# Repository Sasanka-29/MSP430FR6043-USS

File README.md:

# 🫁 Spirometer — MSP430FR6043 USS

> An ultrasonic sensing (USS) based incentive spirometer built on the **TI MSP430FR6043** microcontroller, designed for post-surgical lung rehabilitation and respiratory health monitoring.

---

## 📋 Table of Contents

- [About the Project](#about-the-project)
- [What is an Incentive Spirometer?](#what-is-an-incentive-spirometer)
- [System Architecture](#system-architecture)
- [Hardware](#hardware)
- [Technologies Used](#technologies-used)
- [Data Output Methods](#data-output-methods)
- [Repository Structure](#repository-structure)
- [Getting Started](#getting-started)
- [Roadmap](#roadmap)
- [Contributing](#contributing)
- [License](#license)

---

## 📖 About the Project

This project implements a **digital incentive spirometer** using the **MSP430FR6043** microcontroller's built-in **Ultrasonic Sensing Solution (USS)** module. The USS module measures airflow through an ultrasonic transducer pair, enabling accurate, non-mechanical spirometry readings.

**Key Highlights:**

- 🔊 Ultrasonic time-of-flight (ToF) based flow measurement — no moving parts
- 🎯 Calibrated using the **TI USS Design Center GUI**
- 💻 Firmware developed in **Code Composer Studio (CCS)**
- 📡 Dual data output: **USS GUI** or **UART serial communication**
- 🖥️ Custom **Python GUI** for real-time 4-channel data visualization
- 🔧 Planned migration from the **EVM430-FR6043** evaluation module to a **custom PCB** with hardware optimizations

---

## 💡 What is an Incentive Spirometer?

An **incentive spirometer** is a handheld medical device used to exercise and expand the lungs. It is commonly prescribed:

- **After surgery** — to prevent pulmonary complications during recovery
- **After chest/lung injury** — to restore lung capacity
- **During illness** — to reduce the risk of pneumonia and atelectasis (lung collapse)

The device encourages patients to take slow, deep breaths, helping keep the alveoli (air sacs) open and improving oxygen exchange.

### Why Digitize It?

Traditional incentive spirometers are purely mechanical — a ball or piston rises in a chamber as the patient inhales. This project aims to **digitize** the incentive spirometer using ultrasonic flow sensing, enabling:

| Feature           | Traditional          | This Project                     |
| ----------------- | -------------------- | -------------------------------- |
| Measurement       | Visual (ball height) | Precise digital values           |
| Data Logging      | ❌ None              | ✅ CSV export & real-time graphs |
| Remote Monitoring | ❌ Not possible      | ✅ UART / future wireless        |
| Accuracy          | Approximate          | IEEE 754 float precision         |
| Moving Parts      | Yes (ball/piston)    | None (ultrasonic)                |

---

## 🏗️ System Architecture

```mermaid
flowchart TD
    Transducers["Ultrasonic Transducers<br/>(Upstream & Downstream)"]

    MSP["MSP430FR6043<br/>USS Module (ToF Measurement)<br/>Signal Processing & Firmware"]

    GUI["USS GUI<br/>(TI Design Center)<br/><br/>• Calibration<br/>• Visualization<br/>• Debugging"]

    subgraph UART ["UART Output (Serial → PC)"]
        direction TB
        Script1["uart_parse.py<br/>(CLI batch)"]
        Script2["uart_gui.py<br/>(Live GUI)"]
    end

    Transducers --> MSP
    MSP --> GUI
    MSP --> UART
```

---

## 🔧 Hardware

### Current Development Platform

| Component       | Details                                                                  |
| --------------- | ------------------------------------------------------------------------ |
| **MCU**         | [TI MSP430FR6043](https://www.ti.com/product/MSP430FR6043)               |
| **Dev Board**   | [EVM430-FR6043](https://www.ti.com/tool/EVM430-FR6043) Evaluation Module |
| **Sensing**     | Ultrasonic Sensing Solution (USS) — Time-of-Flight                       |
| **Transducers** | Upstream & downstream ultrasonic transducer pair                         |
| **IDE**         | [Code Composer Studio (CCS)](https://www.ti.com/tool/CCSTUDIO)           |
| **Calibration** | [TI USS Design Center GUI](https://www.ti.com/tool/USS-DESIGN-CENTER)    |

### Planned Custom PCB

The next phase of this project involves designing a **custom PCB** to replace the EVM430-FR6043, with the following goals:

- 🔩 **Hardware optimization** — reduced board size, optimized power routing
- ⚡ **Low power design** — leveraging MSP430FR6043 ultra-low-power modes (LPM3/LPM4)
- 🧩 **Application-specific layout** — tailored for spirometer enclosure integration
- 📡 **Communication interfaces** — UART, potential wireless (BLE/Wi-Fi) add-on
- 🔋 **Battery operation** — portable, handheld device form factor

---

## 🛠️ Technologies Used

### Firmware / Embedded

| Technology           | Purpose                                   |
| -------------------- | ----------------------------------------- |
| MSP430FR6043         | Ultra-low-power MCU with USS module       |
| USS Library          | TI's ultrasonic sensing signal processing |
| Code Composer Studio | IDE for firmware development              |
| USS Design Center    | Transducer calibration & flow config      |

### Software / Host PC

| Technology  | Purpose                            |
| ----------- | ---------------------------------- |
| Python 3.7+ | Host-side data acquisition scripts |
| pyserial    | Serial UART communication          |
| matplotlib  | Real-time 4-channel graph plotting |
| Tkinter     | GUI framework for serial monitor   |

---

## 📤 Data Output Methods

There are **two methods** to obtain spirometry readings from the MSP430FR6043:

### Method 1: USS Design Center GUI

| Aspect          | Details                             |
| --------------- | ----------------------------------- |
| **Connection**  | USB to EVM430-FR6043                |
| **Software**    | TI USS Design Center GUI            |
| **Best For**    | Development, calibration, debugging |
| **Data Format** | Visual plots + internal data export |

### Method 2: UART Communication ⭐

| Aspect          | Details                                                   |
| --------------- | --------------------------------------------------------- |
| **Connection**  | USB/Serial to MSP430FR6043                                |
| **Software**    | `uart_gui.py` (live) or `uart_parse.py` (batch)           |
| **Best For**    | Standalone operation, data logging, integration           |
| **Data Format** | `<delimiter>,<hex IEEE754>` → decoded float               |
| **Channels**    | AbsTof-UPS (`$`), AbsTof-DNS (`#`), DToF (`%`), VFR (`!`) |

> 📖 **See the full UART documentation:** [`Spirometer/UART/README.md`](Spirometer/UART/README.md)

---

## 📁 Repository Structure

```
MSP430FR6043-USS/
│
├── 📄 README.md                            ← You are here
│
└── 📂 Spirometer/
    │
    ├── 📂 GUI/                             ← USS Design Center GUI files
    │   └── README.md                       ← GUI module documentation
    │
    └── 📂 UART/                            ← UART communication module
        ├── 📄 README.md                    ← Detailed UART documentation
        ├── 🐍 uart_parse.py                ← CLI batch hex → float parser
        ├── 🐍 uart_gui.py                  ← Real-time serial monitor GUI
        ├── 📊 hex_in.csv                   ← Sample raw UART data (hex)
        ├── 📊 hex_out.csv                  ← Sample decoded output (float)
        └── 📄 tempCodeRunnerFile.python    ← Dev temp file (VS Code)
```

---

## 🚀 Getting Started

### Prerequisites

| Requirement                  | Link                                                  |
| ---------------------------- | ----------------------------------------------------- |
| Code Composer Studio (CCS)   | [Download](https://www.ti.com/tool/CCSTUDIO)          |
| TI USS Design Center GUI     | [Download](https://www.ti.com/tool/USS-DESIGN-CENTER) |
| EVM430-FR6043 (or custom HW) | [Product Page](https://www.ti.com/tool/EVM430-FR6043) |
| Python 3.7+                  | [Download](https://www.python.org/downloads/)         |
| USB Cable                    | For programming & UART                                |

### Quick Start

1. **Clone the repository**

   ```bash
   git clone https://github.com/Sasanka-29/MSP430FR6043-USS.git
   cd MSP430FR6043-USS
   ```

2. **Install Python dependencies** (for UART tools)

   ```bash
   pip install pyserial matplotlib
   ```

3. **Firmware Setup**
   - Open Code Composer Studio
   - Import the project from the `Spirometer/` directory
   - Connect the EVM430-FR6043 via USB

4. **Calibrate using USS Design Center**
   - Open the USS Design Center GUI
   - Follow the calibration workflow for your transducer configuration

5. **Flash and Run**
   - Build and flash the firmware to the MSP430FR6043

6. **View Output**

   **Option A — USS GUI:**
   Use the TI Design Center for visualization

   **Option B — UART (Recommended for data logging):**

   ```bash
   # Real-time GUI monitor
   cd Spirometer/UART
   python uart_gui.py

   # Or batch parse captured data
   python uart_parse.py hex_in.csv hex_out.csv
   ```

---

## 🗺️ Roadmap

- [x] Initial firmware development on EVM430-FR6043
- [x] USS Design Center GUI calibration
- [x] UART data output implementation
- [x] Python CLI parser (`uart_parse.py`)
- [x] Real-time serial monitor GUI (`uart_gui.py`)
- [x] Custom PCB schematic design
- [x] Custom PCB layout and fabrication
- [x] Hardware optimization and power profiling
- [ ] Enclosure design for handheld spirometer
- [ ] Patient-facing display/indicator integration
- [ ] Wireless data transmission (BLE/Wi-Fi)
- [ ] Mobile app integration

---

## 🤝 Contributing

Contributions are welcome! If you'd like to improve this project:

1. **Fork** the repository
2. **Create** a feature branch (`git checkout -b feature/your-feature`)
3. **Commit** your changes (`git commit -m 'Add your feature'`)
4. **Push** to the branch (`git push origin feature/your-feature`)
5. **Open** a Pull Request

### Ideas for Contribution

- 📐 Custom PCB design files (KiCad/Altium)
- 📱 Mobile app for Bluetooth data reception
- 📊 Advanced spirometry analytics (FEV1, FVC calculation)
- 🧪 Unit tests for the Python parsing scripts
- 📝 Additional documentation or translations

---

## 📄 License

Distributed under the MIT License. See [`LICENSE`](LICENSE) for more information.

---

## 📚 References

- [MSP430FR6043 Product Page](https://www.ti.com/product/MSP430FR6043) — TI microcontroller datasheet & resources
- [USS Design Center User Guide](https://www.ti.com/tool/USS-DESIGN-CENTER) — Calibration and configuration tool
- [EVM430-FR6043 User Guide](https://www.ti.com/tool/EVM430-FR6043) — Evaluation module documentation
- [MSP430 USS Application Report (SLAA720)](https://www.ti.com/lit/an/slaa720c/slaa720c.pdf) — Ultrasonic sensing implementation guide

---

<p align="center">
  <b>Designed & Developed by <a href="https://github.com/Sasanka-29">Sasanka-29</a></b><br>
  <i>MSP430FR6043 Ultrasonic Sensing Solution — Incentive Spirometer</i><br><br>
  ⭐ Star this repo if you find it useful!
</p>

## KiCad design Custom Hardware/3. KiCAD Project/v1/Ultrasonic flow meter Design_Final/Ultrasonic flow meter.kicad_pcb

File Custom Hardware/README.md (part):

# MSP430FR6043 USS - Custom Hardware Documentation

## Overview

This directory contains the **complete custom hardware design assets, documentation, and validation records** for the `MSP430FR6043_USS` project. It supports development, validation, and long-term maintenance of hardware built around the **Texas Instruments MSP430FR6043** microcontroller with **Ultrasonic Sensing Solution (USS)** capabilities.

> **For Firmware/Software:** Refer to the repository root and source directories for application code, bootloader, and USS driver implementations.  
> **This folder focuses on:** Board-level hardware artifacts, schematics, PCB layouts, BOMs, bring-up procedures, and validation evidence.

---

## Table of Contents

1. [Project Objectives](#1-project-objectives)
2. [Hardware Overview](#2-hardware-overview)
3. [Design Principles](#3-design-principles)
4. [Directory Structure](#4-directory-structure)
5. [Hardware Revisions](#5-hardware-revisions)
6. [Pin Assignment & Interfaces](#6-pin-assignment--interfaces)
7. [Power, Ground & Clock Design](#7-power-ground--clock-design)
8. [Programming & Bring-Up Procedure](#8-programming--bring-up-procedure)
9. [Validation & Testing](#9-validation--testing)
10. [Manufacturing Checklist](#10-manufacturing-checklist)
11. [Bill of Materials (BOM)](#11-bill-of-materials-bom)
12. [Firmware Compatibility](#12-firmware-compatibility)
13. [Known Issues & Limitations](#13-known-issues--limitations)
14. [Contributing Guidelines](#14-contributing-guidelines)
15. [To Do & Future Work](#15-to-do--future-work)
16. [References & Resources](#16-references--resources)
17. [Maintenance & Handoff](#17-maintenance--handoff)
18. [License & Compliance](#18-license--compliance)

---

## 1) Project Objectives

The MSP430FR6043 USS custom hardware platform enables:

### Primary Goals
- **Prototype Development:** Rapid hardware iteration for ultrasonic sensing applications
- **Performance Validation:** Characterize power consumption, signal integrity, and real-time behavior
- **Peripheral Integration:** Test and validate all external interfaces (UART, GPIO, analog inputs, programming headers)
- **Hardware-Firmware Co-Development:** Ensure seamless integration between hardware design and firmware implementation
- **Reproducibility:** Create a baseline for manufacturing, field deployment, and long-term support

### Key Principles
- **Traceability:** Every design decision is documented with rationale and evidence
- **Reproducibility:** Future developers can rebuild and validate with confidence
- **Maintainability:** Clear documentation minimizes debug cycles and institutional knowledge loss
- **Scalability:** Support multiple board revisions while maintaining backward compatibility

---

## 2) Hardware Overview

### System Architecture

The MSP430FR6043 platform consists of:

| Subsystem | Components | Purpose |
|-----------|-----------|---------|
| **MCU Core** | MSP430FR6043 + support circuitry | Primary processing and USS interface |
| **Power Distribution** | Voltage regulators, decoupling capacitors, protection circuits | Stable supply for analog and digital domains |
| **Clock Network** | Crystal oscillator, load capacitors | Precise timing for USS and real-time operations |
| **Debug Interface** | JTAG/SBW header, test points | Programming and in-circuit debugging |
| **Ultrasonic Front-End** | Transducer interface, signal conditioning | USS signal acquisition and processing |
| **I/O & Test Points** | Headers, connectors, measurement hooks | System bring-up and signal observation |

### Design Constraints
- Low-noise analog performance (USS operates in 40-100 kHz range)
- Low-power operation (MSP430FR6043 FRAM architecture)
- Reliable programming access (no conflicts with application I/O)
- Practical manufacturability and PCB testability

---

## 3) Design Principles

### Analog Signal Integrity
1. Separate analog and digital ground planes where applicable
2. Keep USS signal paths isolated from high-speed digital switching
3. Place decoupling capacitors within 5mm of supply pins
4. Use star grounding at measurement reference points

### Power Management
1. Clean regulated supplies for both analog and digital domains
2. Adequate bulk and bypass capacitance per datasheet recommendations
3. Transient protection for external inputs (ESD, overcurrent)
4. Isolation strategy for programming pins from application circuitry

### Clock Design
1. Crystal oscillator with proper load matching
2. Minimal EMI radiation from clock traces
3. Startup verification at multiple supply voltages
4. Characterization data recorded for production batches

---

## 4) Directory Structure

Current folder organization:

```
Custom Hardware/
├── README.md                              # This file
├── Custom Board Connections/              # Board-level connection documentation and interfaces
├── Issues and Fixes for Custom Boards/    # Known issues, bug reports, and resolution procedures
├── KiCAD Project/                         # KiCAD schematic and PCB design files
├── Spirometer latest 3D Files/            # 3D CAD models and mechanical drawings for enclosure/mounting
├── Spirometer Dimension diagram/          # Dimensional specifications and mechanical diagrams
├── Assembly Guide/                        # Hardware assembly instructions and procedures
├── Zero Flow Calibration Setup/           # Calibration procedures and reference data
└── Results/                               # Test results, validation data, and performance logs
```

### Folder Descriptions

- **Custom Board Connections:** Documentation of all board connectors, headers, and external interfaces
- **Issues and Fixes for Custom Boards:** Hardware issues discovered during development, troubleshooting guides, and workarounds
- **KiCAD Project:** Complete KiCAD project files including schematics, PCB layouts, and design outputs
- **Spirometer latest 3D Files:** 3D CAD models for mechanical components, enclosure designs, and mounting brackets
- **Spirometer Dimension diagram:** Technical drawings with dimensional specifications and mechanical tolerances
- **Assembly Guide:** Step-by-step hardware assembly procedures, BOM details, and bring-up procedures
- **Zero Flow Calibration Setup:** Calibration baseline data and procedures for zero-flow reference conditions
- **Results:** Performance validation results, power measurements, USS characterization logs, and test reports

---

## 5) Hardware Revisions

### Revision Tracking Table

| Revision | Status | Release Date | Summary | Key Changes | Firmware Impact | Validation |
|----------|--------|--------------|---------|------------|-----------------|------------|
| REV_A | Released | TBD | Initial prototype | First production run | Baseline | Complete |
| REV_B | Planning | TBD | Analog improvements | Front-end filtering updates | Recalibration | Pending |

### For Each Revision, Document:
- **Design Changes:** Specific modifications and rationale
- **Affected Signals:** Which nets/interfaces changed
- **Firmware Implications:** Pin mappings, calibration constants, driver updates
- **Validation Evidence:** Test data, measurements, approval sign-offs
- **Known Issues:** Bugs, workarounds, or limitations specific to this revision

---

## 6) Pin Assignment & Interfaces

### MCU Pin Mapping

Maintain a detailed pin-assignment matrix (create `Pin_Assignment_Matrix.xlsx` or similar):

| MCU Pin | Signal Name | Board Function | Peripheral | Firmware Symbol | Schematic Reference | Notes |
|---------|------------|-----------------|------------|-----------------|-------------------|-------|
| P1.0 | GPIO_0 | Example I/O | GPIO | PIN_IO_0 | U1-1 | TBD |
| P2.0 | USS_RX | Ultrasonic RX | USS | PIN_USS_RX | J1-2 | Analog input |

### External Interfaces

Document all connectors and headers:

- **Power Input:** Voltage requirements, polarity, protection
- **Debug/JTAG:** Pin layout, support toolchain
- **UART/Serial:** Baud rates, connector type
- **Analog Inputs/Outputs:** Signal ranges, impedance, termination
- **Test Points:** Measurement access points with expected voltage ranges

---

## 7) Power, Ground & Clock Design

### Power Distribution

**Supply Rails:**
- Input voltage range: [TBD] V
- Regulated output: [TBD] V @ [TBD] mA max
- Quiescent current: [TBD] mA (typical)

**Decoupling Strategy:**
- MCU supply: 100nF + 10µF (close placement)
- Analog supply: 100nF + 10µF (if separate)
- Bulk capacitance: 47µF (for transient loading)

### Ground Design
- Multi-point ground connection at board entry
- Ground plane continuity under critical traces
- Star grounding at measurement reference points

### Clock Network
- **Oscillator Frequency:** [TBD] MHz
- **Load Capacitance:** [TBD] pF
- **Startup Time:** < [TBD] ms
- **Frequency Stability:** ±[TBD] ppm

### Measured Characteristics (per revision)
- Rail ripple and transient response
- Startup behavior and settling time
- Current profiles by operational mode
- Temperature/voltage drift (if applicable)

---

## 8) Programming & Bring-Up Procedure

### Pre-Power Checklist
- [ ] Visual inspection: polarity, solder joints, shorts
- [ ] Continuity check on critical nets
- [ ] No visible damage or bridged pads

### Power-On Validation
- [ ] Apply input voltage slowly (observe current ramp)
- [ ] Measure all regulated rails and confirm nominal values
- [ ] Check quiescent current against expectations
- [ ] Verify no shorts (current should plateau)

### Programming & Debug
- [ ] Connect JTAG/SBW debugger
- [ ] Verify connection in IDE or debugger software
- [ ] Flash known-good test image
- [ ] Verify successful programming (LED blink test, etc.)

### Peripheral Validation
- [ ] UART loopback test (if applicable)
- [ ] GPIO output test (LED flash, test point measurement)
- [ ] Timer/counter verification
- [ ] Analog input verification (known voltage sources)

### USS Functional Test
- [ ] Connect transducer or known signal source
- [ ] Run USS calibration routine
- [ ] Compare output signatures with baseline
- [ ] Document results and save logs

### Post-Validation
- [ ] Document board ID, test date, operator name
- [ ] Archive photos (top, bottom, detail shots)
- [ ] Save measurement data and logs
- [ ] Mark board as "ready for deployment" or "needs rework"

---

## 9) Validation & Testing

### Required Evidence per Revision

Each board revision must include:

- **Bring-Up Logs:** Dated records with board ID, firmware hash, test results
- **Power Measurements:** Active/idle/LPM current, rail ripple, startup transients
- **Oscillator Characterization:** Frequency, stability across voltage/temperature
- **USS Validation:** Functional signatures, calibration data, response plots
- **Peripheral Tests:** UART, GPIO, timer, analog, all working as documented
- **Failure Analysis:** Any issues encountered, root cause, resolution

### Validation Checklist
- [ ] Board photos (top, bottom, detail)
- [ ] Power rails measured and documented
- [ ] Program successful with known-good image
- [ ] All peripherals respond correctly
- [ ] USS functional with baseline transducer
- [ ] No unexpected behavior or regressions
- [ ] Logs and measurement data archived

---

## 10) Manufacturing Checklist

Before release to fabrication or production:

### Design Verification
- [ ] Schematic schematic reviewed and approved
- [ ] ERC (electrical rule check) passed
- [ ] DRC (design rule check) passed on PCB
- [ ] Design review sign-off documented

### Fabrication Package
- [ ] Gerber files generated and verified
- [ ] Drill file included with correct formats
- [ ] Soldermask/silkscreen layers correct
- [ ] PCB stackup and layer order documented
- [ ] File naming consistent (REV tag in filenames)

### Assembly Package
- [ ] BOM exported with MPN, manufacturer, quantity
- [ ] Pick-and-place file generated
- [ ] Assembly drawing with reference designators
- [ ] Component orientation clearly marked
- [ ] All footprints match BOM parts

### Quality & Testing
- [ ] Test-point map generated
- [ ] Bring-up procedure finalized
- [ ] Test image and firmware version noted
- [ ] Acceptance criteria defined
- [ ] Quality checklist ready for manufacturing

---

## 11) Bill of Materials (BOM)

### BOM Format

Maintain BOM as `BOM_REV_X.xlsx` or `.csv` with columns:

| Item | Reference(s) | Description | Manufacturer | MPN | Alt. MPN | Package | Qty | Unit Cost | Lead Time | Lifecycle | Risk Notes |
|------|---------|-------------|----------|-----|----------|---------|-----|-----------|-----------|-----------|-----------|
| 1 | U1 | MCU | Texas Instruments | MSP430FR6043IRHAT | - | LQFP-64 | 1 | $[TBD] | [TBD] weeks | Active | Low |

### Critical BOM Notes
- **Lifecycle Status:** Active / NRND / Obsolete
- **Approved Alternates:** Part numbers with compatible footprints/function
- **Supply Constraints:** Single-source risks, long lead items
- **Environmental:** Temperature ratings, RoHS compliance, moisture sensitivity

---

## 12) Firmware Compatibility

### Compatibility Matrix

| Hardware Revision | Firmware Version/Tag | Tested By | Date | Notes | Calibration Required |
|------------------|------------------|-----------|------|-------|----------------------|
| REV_A | v1.0.0 | [Name] | [Date] | Initial release | Yes |
| REV_B | v1.1.0+ | [Name] | [Date] | Updated front-end filtering | Yes |

### Version Management
- Tag firmware releases that are validated for each hardware revision
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
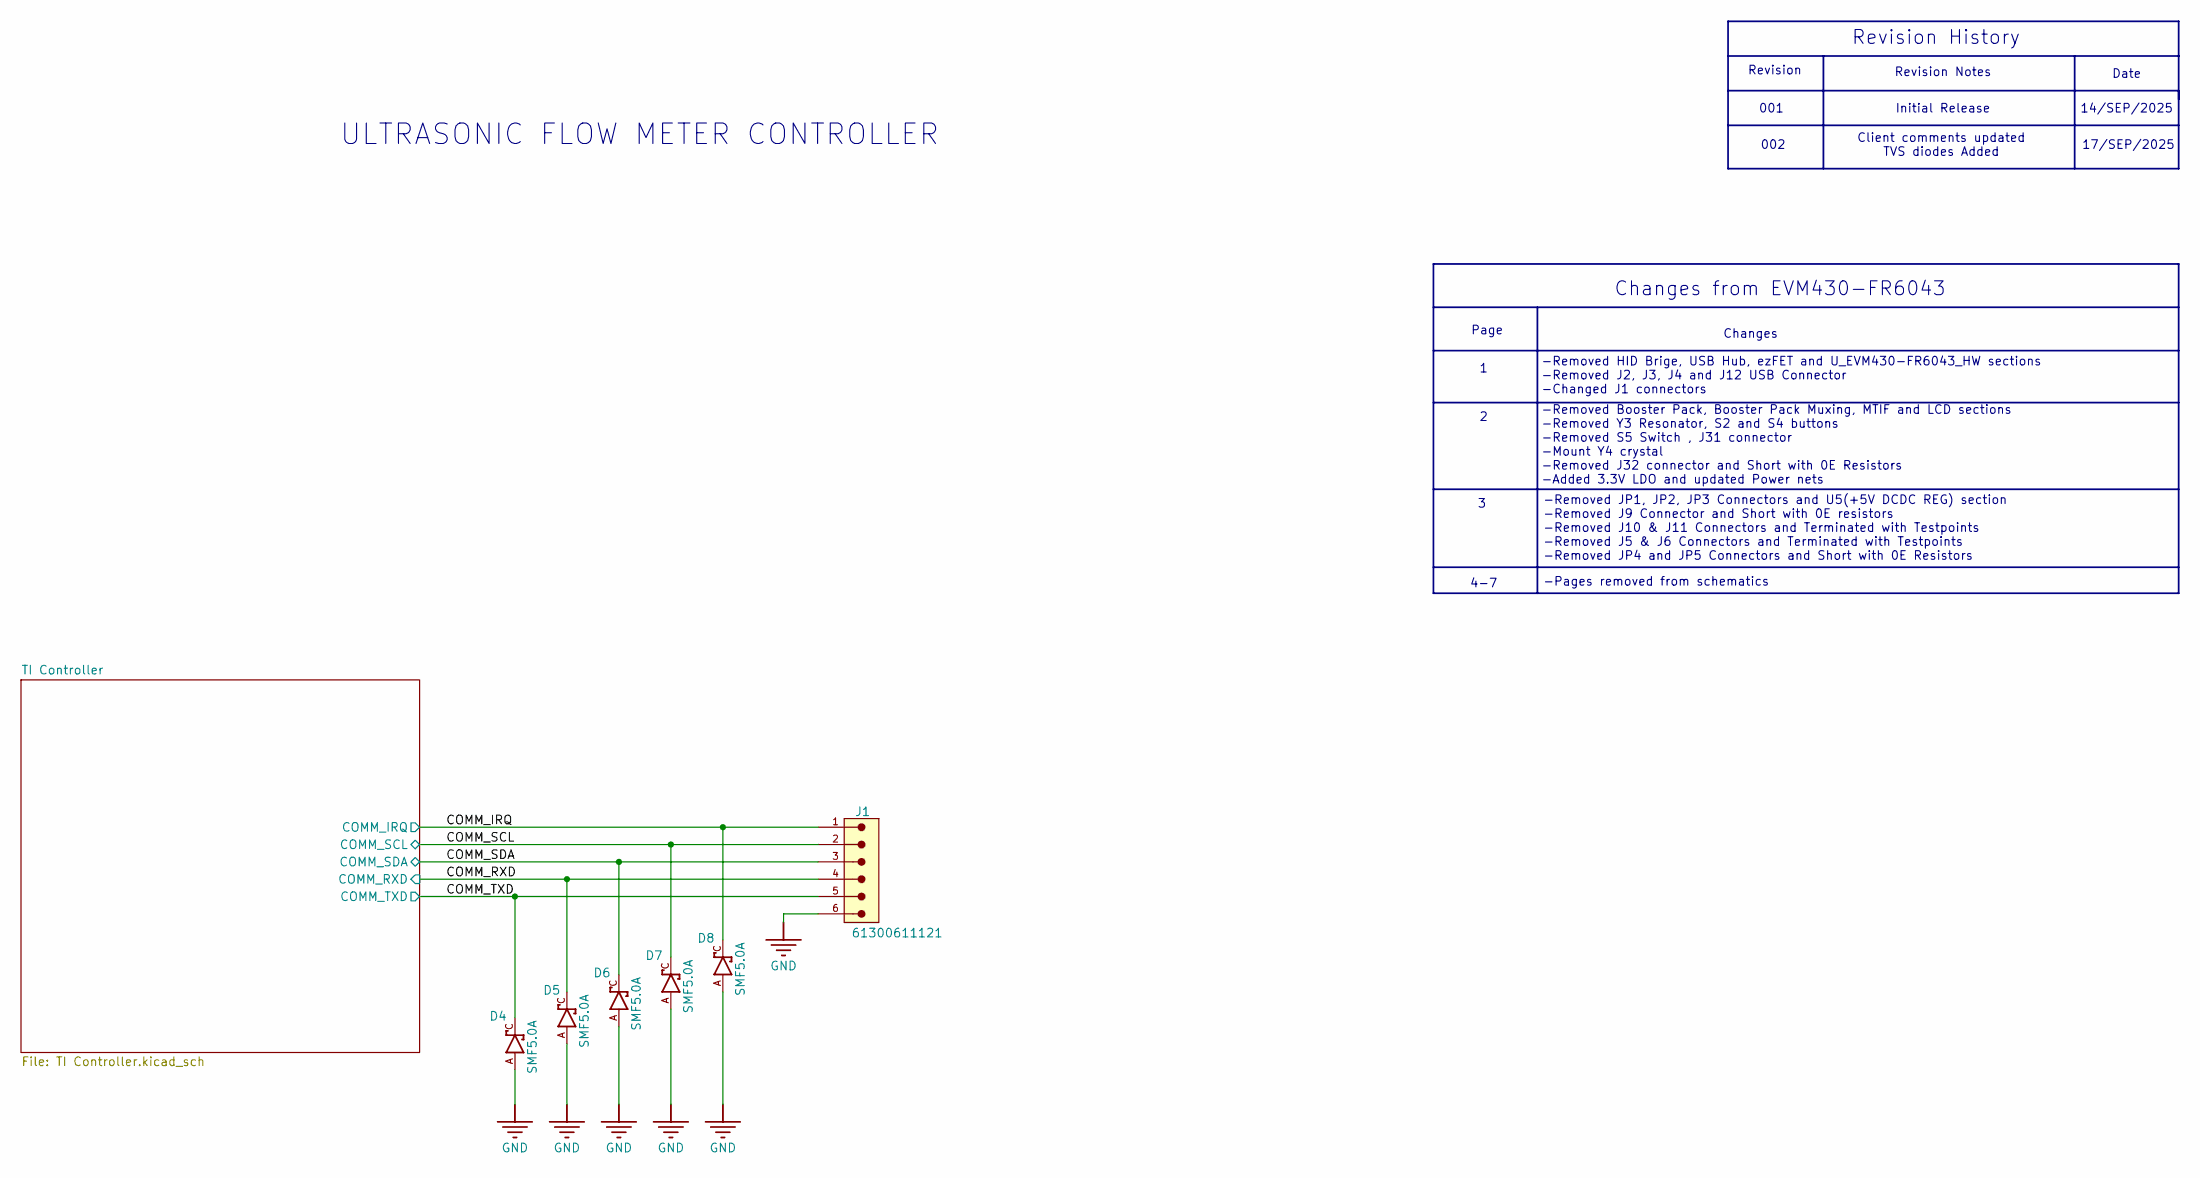
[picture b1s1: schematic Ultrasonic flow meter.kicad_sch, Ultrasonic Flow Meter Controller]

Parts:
D4, D5, D6, D7, D8: SMF5.0A; SOD3718X102N
J1: 61300611121; PARTNUMBER 61300611121

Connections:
/COMM_IRQ: D8.C, J1.1; also elsewhere on the board
/COMM_RXD: D5.C, J1.4; also elsewhere on the board
/COMM_SCL: D7.C, J1.2; also elsewhere on the board
/COMM_SDA: D6.C, J1.3; also elsewhere on the board
/COMM_TXD: D4.C, J1.5; also elsewhere on the board
GND: D4.A, D5.A, D6.A, D7.A, D8.A, J1.6; also elsewhere on the board

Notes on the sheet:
Page
Revision History
Revision Notes
Date
-Removed Booster Pack, Booster Pack Muxing, MTIF and LCD sections -Removed Y3 Resonator, S2 and S4 buttons -Removed S5 Switch , J31 connector -Mount Y4 crystal -Removed J32 connector and Short with 0E Resistors -Added 3.3V LDO and updated Power nets
-Removed JP1, JP2, JP3 Connectors and U5(+5V DCDC REG) section -Removed J9 Connector and Short with 0E resistors -Removed J10 & J11 Connectors and Terminated with Testpoints -Removed J5 & J6 Connectors and Terminated with Testpoints -Removed JP4 and JP5 Connectors and Short with 0E Resistors
ULTRASONIC FLOW METER CONTROLLER
001
Changes
-Removed HID Brige, USB Hub, ezFET and U_EVM430-FR6043_HW sections -Removed J2, J3, J4 and J12 USB Connector -Changed J1 connectors
14/SEP/2025
002
Changes from EVM430-FR6043
17/SEP/2025
Initial Release
Revision
Client comments updated TVS diodes Added
-Pages removed from schematics
4-7

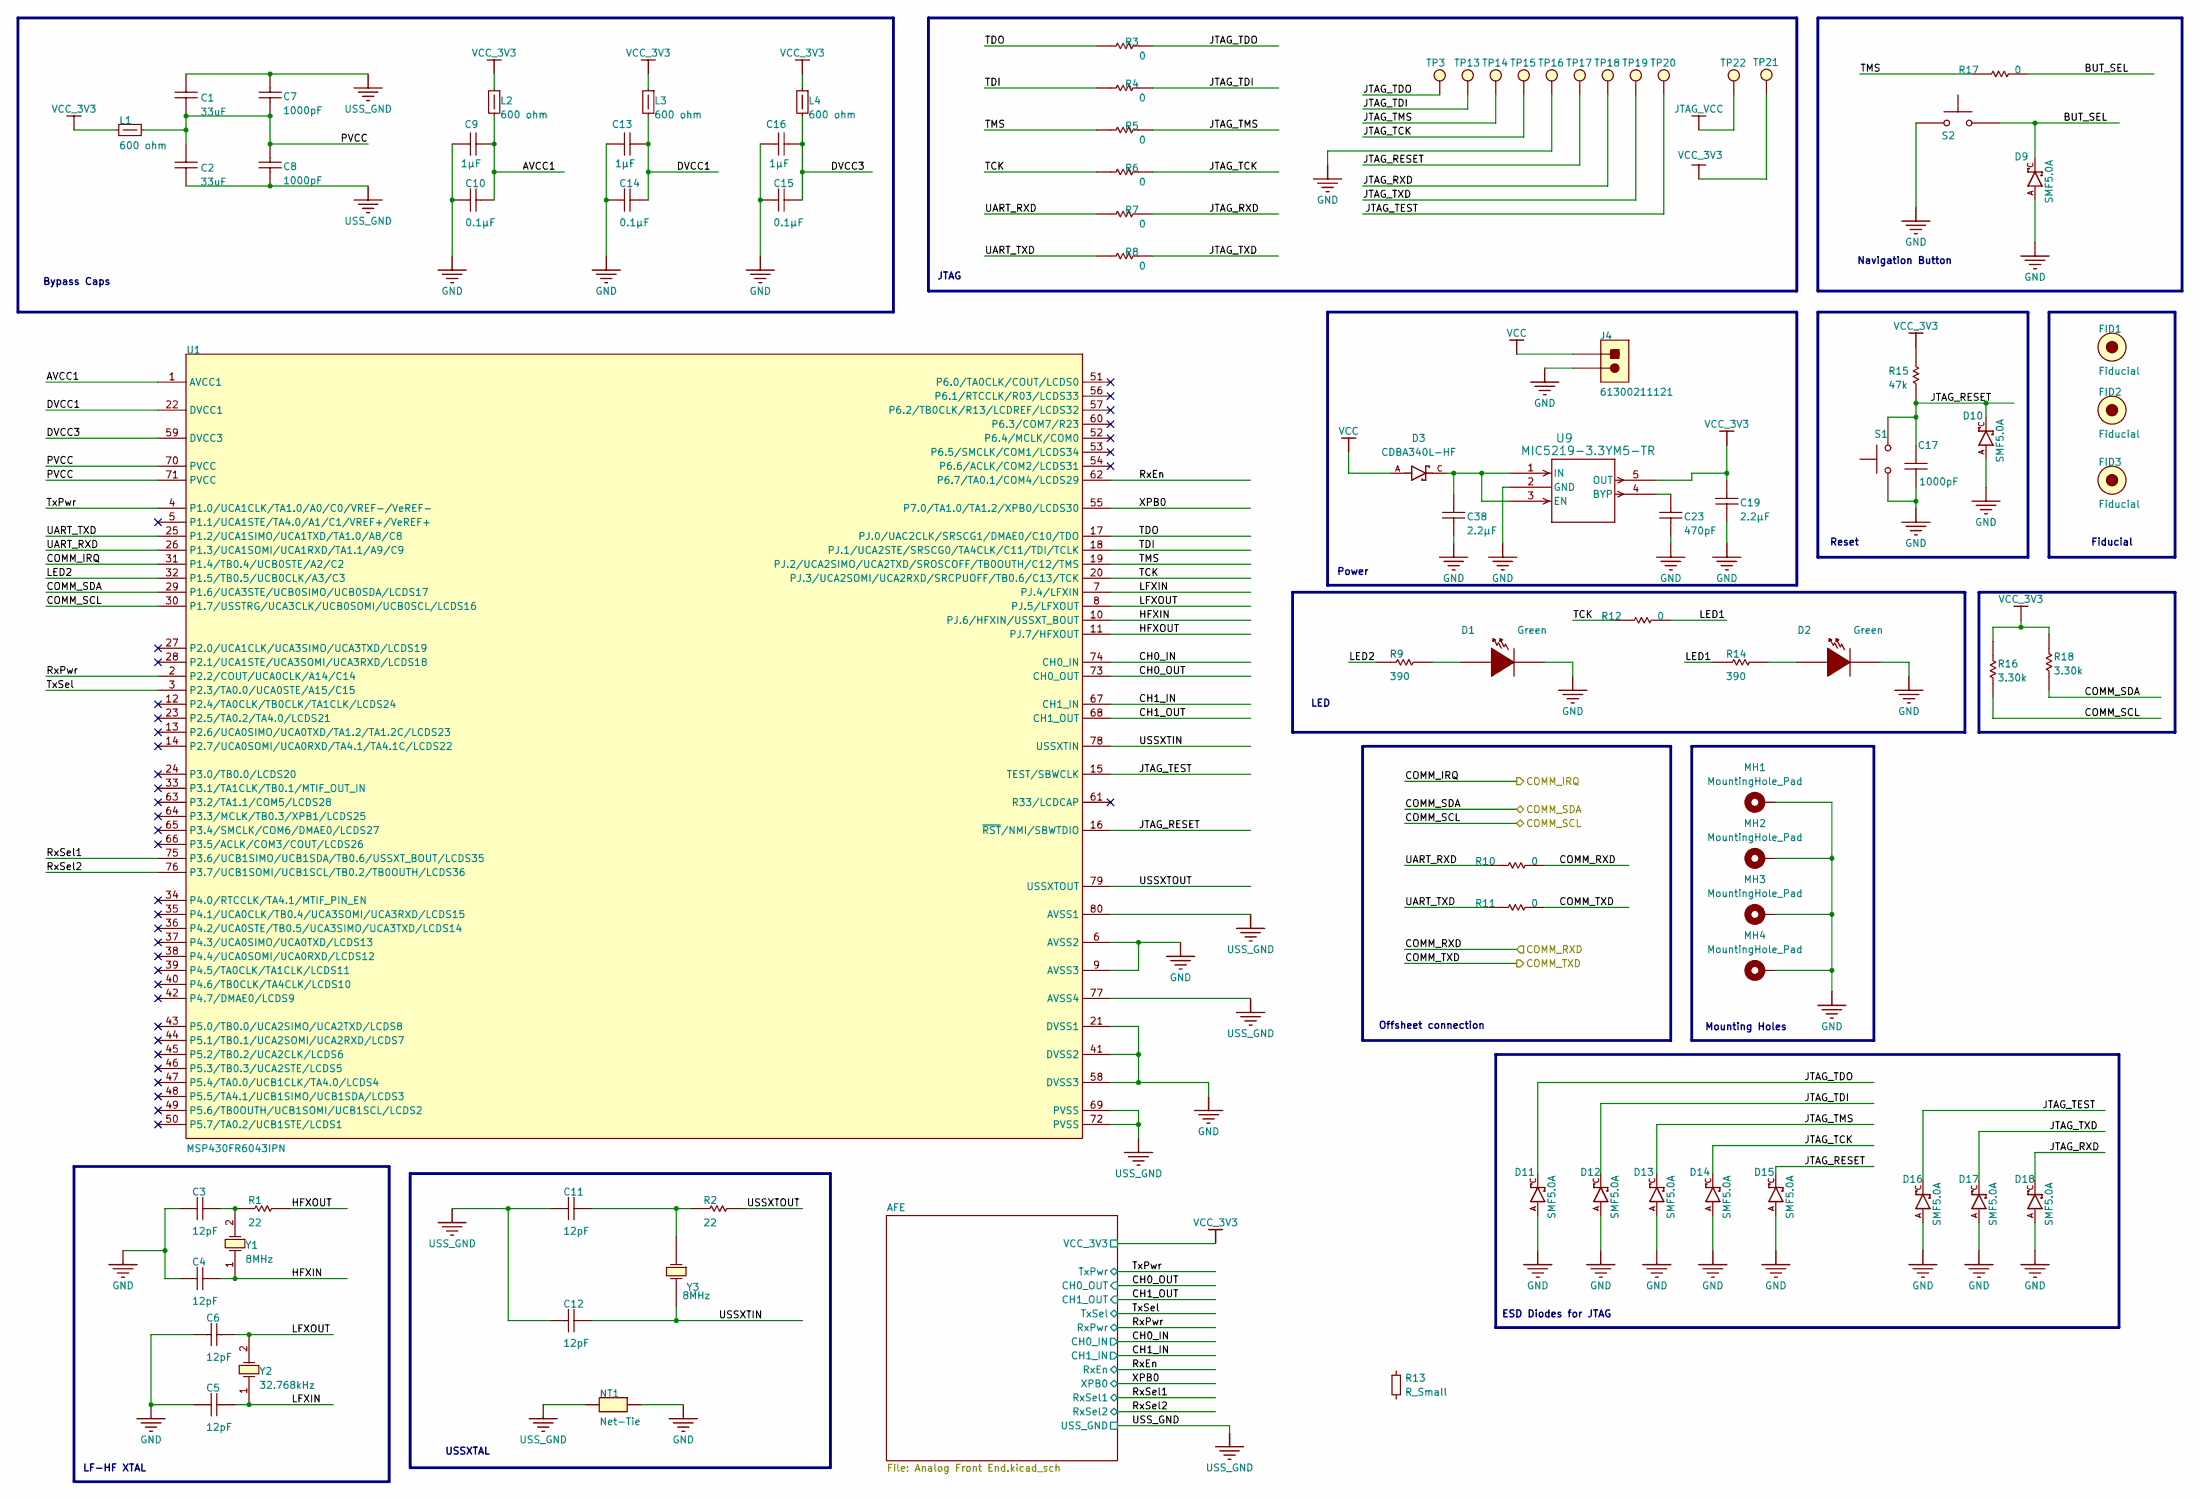
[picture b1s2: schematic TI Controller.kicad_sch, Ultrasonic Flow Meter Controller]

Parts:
C1, C2: C2012X5R1A336M125AC; 0805; TOLERANCE_% 20%; PARTNUMBER C2012X5R1A336M125AC
C3, C4, C5, C6, C11, C12: GRM1555C1H120JA01D; 0402; TOLERANCE_% 5; PARTNUMBER GRM1555C1H120JA01D
C7, C8, C17: GRM1555C1H102JA01D; 0402S; TOLERANCE_% 5; PARTNUMBER GRM1555C1H102JA01D
C9, C13, C16: CL10B105KO8NNNC; 0603L; TOLERANCE_% 10; PARTNUMBER CL10B105KO8NNNC
C10, C14, C15: GRM155R71C104KA88D; 0402; TOLERANCE_% 10; PARTNUMBER GRM155R71C104KA88D
C19, C38: GRM188R61C225KE15D; 0603; TOLERANCE_% 10; PARTNUMBER GRM188R61C225KE15D
C23: C0603C471J5GACTU; 0603L; TOLERANCE_% 5; PARTNUMBER C0603C471J5GACTU
D1, D2: LTST-C191TGKT; LTST-C191_Green; PARTNUMBER LTST-C191TGKT
D3: CDBA340L-HF; DIOM5225X250N; PARTREV D
D9, D10, D11, D12, D13, D14, D15, D16, D17, D18: SMF5.0A; SOD3718X102N
FID1, FID2, FID3: Fiducial; Fiducial10-30; PARTNUMBER N/A
J4: 61300211121; WURTH_61300211121; PARTNUMBER 61300211121
L1, L2, L3, L4: MPZ2012S601A; 0805L; PARTNUMBER MPZ2012S601A
MH1, MH2, MH3, MH4: MountingHole_Pad; M2_MH
NT1: Net-Tie; Net-Tie_50milWide_30milLong
R1, R2: CRCW040222R0JNED; 0402S; TOLERANCE_% 5; PARTNUMBER CRCW040222R0JNED
R3, R4, R5, R6, R7, R8, R10, R11, R12, R17: CRCW04020000Z0ED; 0402S; TOLERANCE_% 5; PARTNUMBER CRCW04020000Z0ED
R9, R14: CRCW0402390RJNED; 0402S; TOLERANCE_% 5; PARTNUMBER CRCW0402390RJNED
R13: R_Small; R_0201_0603Metric
R15: CRCW040247K0JNED; 0402S; TOLERANCE_% 5; PARTNUMBER CRCW040247K0JNED
R16, R18: RK73H1ETTP3301F; 0402; TOLERANCE_% 1; PARTNUMBER RK73H1ETTP3301F
S1, S2: B3U-1000P; SW_B3U-1000P; PARTNUMBER B3U-1000P
TP3, TP13, TP14, TP15, TP16, TP17, TP18, TP19, TP20, TP21, TP22: TP_2MM
U1: MSP430FR6043IPN; PN0080A_N; PARTNUMBER MSP430FR6043IPN
U9: MIC5219-3.3YM5-TR; SOT-23-5_M5_MCH-L
Y1: ABM3-8.000MHZ-D2Y-T; Abracon_ABM3; PARTNUMBER ABM3-8.000MHZ-D2Y-T
Y2: ABS07-32.768KHZ-9-T; XTAL_ABS07; PARTNUMBER ABS07-32.768KHZ-9-T
Y3: ABLS-8.000MHZ-B4-T; XTAL_CSM-7X; PARTNUMBER ABLS-8.000MHZ-B4-T

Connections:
/COMM_IRQ: U1.31 (P1.4/TB0.4/UCB0STE/A2/C2); also elsewhere on the board
/COMM_RXD: R10.1; also elsewhere on the board
/COMM_SCL: R16.1, U1.30 (P1.7/USSTRG/UCA3CLK/UCB0SOMI/UCB0SCL/LC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); also elsewhere on the board
/COMM_SDA: R18.1, U1.29 (P1.6/UCA3STE/UCB0SIMO/UCB0SDA/LCDS17); also elsewhere on the board
/COMM_TXD: R11.1; also elsewhere on the board
/TI Controller/AVCC1: C9.1, C10.1, L2.1, U1.1 (AVCC1)
/TI Controller/BUT_SEL: D9.C, R17.1, S2.2
/TI Controller/CH0_IN: U1.74 (CH0_IN); also elsewhere on the board
/TI Controller/CH0_OUT: U1.73 (CH0_OUT); also elsewhere on the board
/TI Controller/CH1_IN: U1.67 (CH1_IN); also elsewhere on the board
/TI Controller/CH1_OUT: U1.68 (CH1_OUT); also elsewhere on the board
/TI Controller/DVCC1: C13.1, C14.2, L3.1, U1.22 (DVCC1)
/TI Controller/DVCC3: C15.1, C16.1, L4.1, U1.59 (DVCC3)
/TI Controller/HFXIN: C4.1, U1.10 (PJ.6/HFXIN/USSXT_BOUT), Y1.1 (OSC1)
/TI Controller/HFXOUT: R1.2, U1.11 (PJ.7/HFXOUT)
/TI Controller/JTAG_RESET: C17.1, D10.C, D15.C, R15.1, S1.2, TP17.1, U1.16 (~RST/NMI/SBWTDIO)
/TI Controller/JTAG_RXD: D18.C, R7.1, TP18.1
/TI Controller/JTAG_TCK: D14.C, R6.1, TP15.1
/TI Controller/JTAG_TDI: D12.C, R4.1, TP13.1
/TI Controller/JTAG_TDO: D11.C, R3.1, TP3.1
/TI Controller/JTAG_TEST: D16.C, TP20.1, U1.15 (TEST/SBWCLK)
/TI Controller/JTAG_TMS: D13.C, R5.1, TP14.1
/TI Controller/JTAG_TXD: D17.C, R8.1, TP19.1
/TI Controller/LED1: R12.1, R14.1
/TI Controller/LED2: R9.1, U1.32 (P1.5/TB0.5/UCB0CLK/A3/C3)
/TI Controller/LFXIN: C5.1, U1.7 (PJ.4/LFXIN), Y2.1 (OSC1)
/TI Controller/LFXOUT: C6.2, U1.8 (PJ.5/LFXOUT), Y2.2 (OSC2)
/TI Controller/PVCC: C1.2, C2.1, C7.2, C8.1, L1.2, U1.70 (PVCC), U1.71 (PVCC)
/TI Controller/RxEn: U1.62 (P6.7/TA0.1/COM4/LCDS29); also elsewhere on the board
/TI Controller/RxPwr: U1.2 (P2.2/COUT/UCA0CLK/A14/C14); also elsewhere on the board
/TI Controller/RxSel1: U1.75 (P3.6/UCB1SIMO/UCB1SDA/TB0.6/USSXT_BOUT/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); also elsewhere on the board
/TI Controller/RxSel2: U1.76 (P3.7/UCB1SOMI/UCB1SCL/TB0.2/TB0OUTH/LCD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); also elsewhere on the board
/TI Controller/TCK: R6.2, R12.2, U1.20 (PJ.3/UCA2SOMI/UCA2RXD/SRCPUOFF/TB0.6/C1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)
/TI Controller/TDI: R4.2, U1.18 (PJ.1/UCA2STE/SRSCG0/TA4CLK/C11/TDI/TCLK)
/TI Controller/TDO: R3.2, U1.17 (PJ.0/UAC2CLK/SRSCG1/DMAE0/C10/TDO)
/TI Controller/TMS: R5.2, R17.2, U1.19 (PJ.2/UCA2SIMO/UCA2TXD/SROSCOFF/TB0OUTH/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)
/TI Controller/TxPwr: U1.4 (P1.0/UCA1CLK/TA1.0/A0/C0/VREF-/VeREF-); also elsewhere on the board
/TI Controller/TxSel: U1.3 (P2.3/TA0.0/UCA0STE/A15/C15); also elsewhere on the board
/TI Controller/UART_RXD: R7.2, R10.2, U1.26 (P1.3/UCA1SOMI/UCA1RXD/TA1.1/A9/C9)
/TI Controller/UART_TXD: R8.2, R11.2, U1.25 (P1.2/UCA1SIMO/UCA1TXD/TA1.0/A8/C8)
/TI Controller/USSXTIN: C12.1, U1.78 (USSXTIN), Y3.1 (OSC1)
/TI Controller/USSXTOUT: R2.2, U1.79 (USSXTOUT)
/TI Controller/XPB0: U1.55 (P7.0/TA1.0/TA1.2/XPB0/LCDS30); also elsewhere on the board
GND: C3.2, C4.2, C5.2, C6.1, C9.2, C10.2, C13.2, C14.1, C15.2, C16.2, C17.2, C19.2, C23.2, C38.2, D1.2 (K), D2.2 (K), D9.A, D10.A, D11.A, D12.A, D13.A, D14.A, D15.A, D16.A, D17.A, D18.A, J4.2, MH1.1, MH2.1, MH3.1, MH4.1, NT1.2, S1.1, S2.1, TP16.1, U1.6 (AVSS2), U1.9 (AVSS3), U1.21 (DVSS1), U1.41 (DVSS2), U1.58 (DVSS3), U9.2 (GND); also elsewhere on the board
JTAG_VCC: TP22.1
unnamed: D1.1 (A), R9.2
unnamed: D2.1 (A), R14.2
unnamed: C23.1, U9.4 (BYP)
unnamed: C38.1, D3.C, U9.1 (IN), U9.3 (EN)
unnamed: C3.1, R1.1, Y1.2 (OSC2)
unnamed: C11.1, R2.1, Y3.2 (OSC2)
USS_GND: C1.1, C2.2, C7.1, C8.2, C11.2, C12.2, NT1.1, U1.69 (PVSS), U1.72 (PVSS), U1.77 (AVSS4), U1.80 (AVSS1); also elsewhere on the board
VCC: D3.A, J4.1
VCC_3V3: C19.1, L1.1, L2.2, L3.2, L4.2, R15.2, R16.2, R18.2, TP21.1, U9.5 (OUT); also elsewhere on the board

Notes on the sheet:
USSXTAL
Fiducial
Power
LF-HF XTAL
Mounting Holes
LED
Bypass Caps
JTAG
Navigation Button
Reset
Offsheet connection
ESD Diodes for JTAG

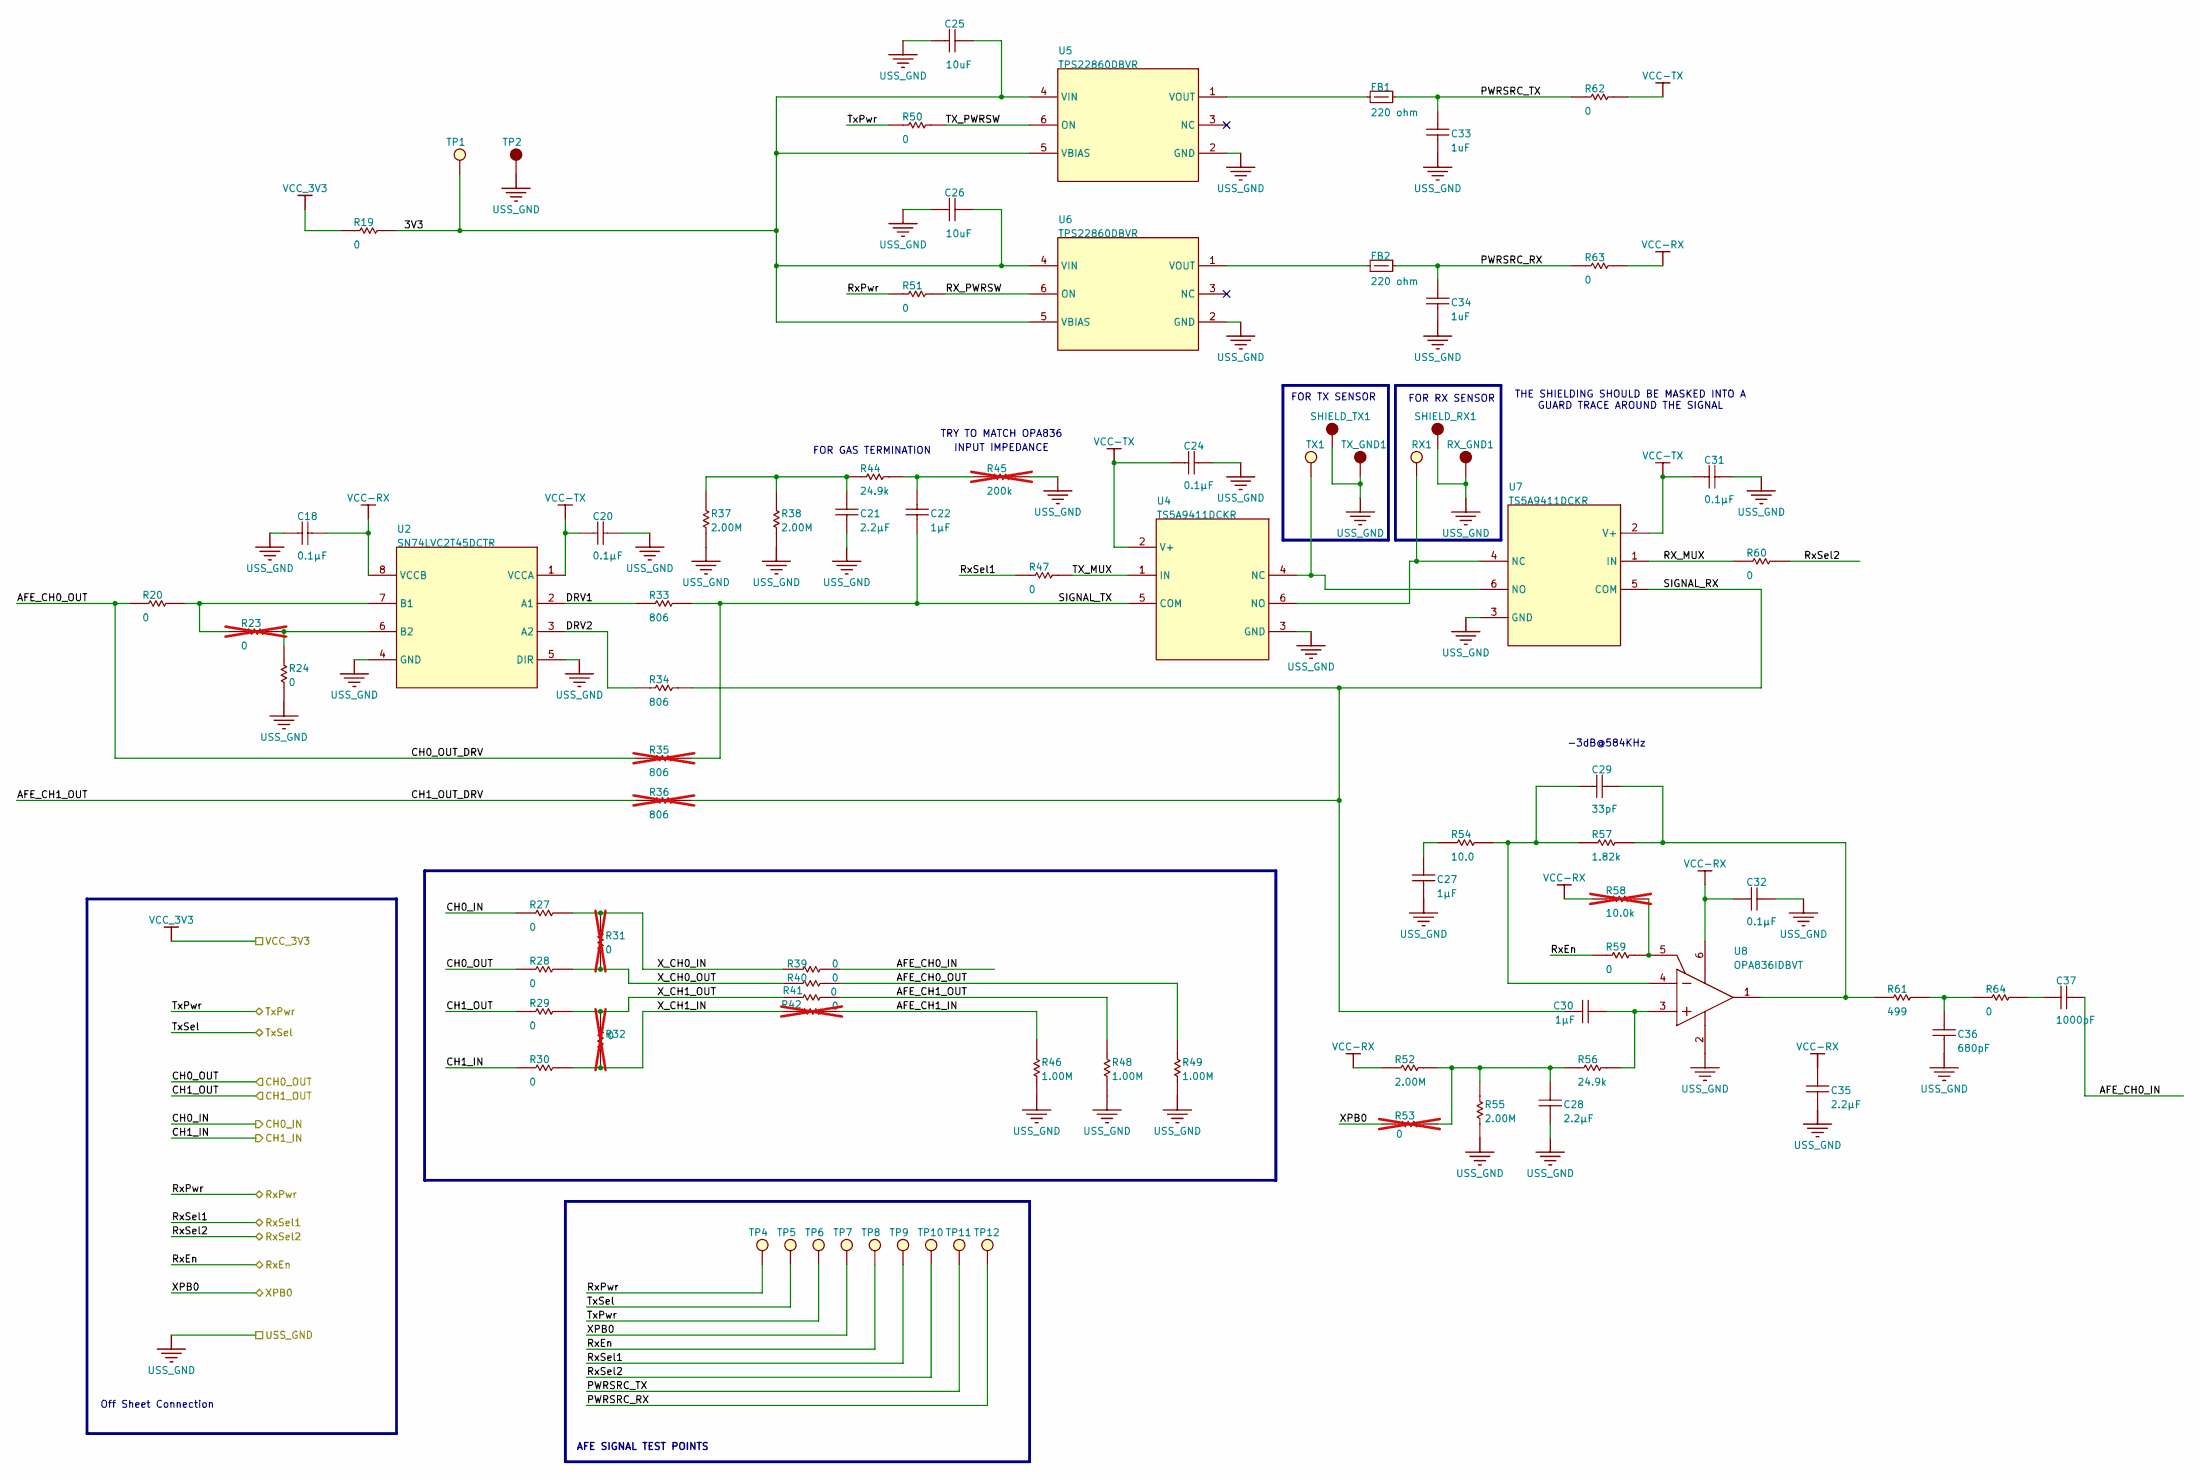
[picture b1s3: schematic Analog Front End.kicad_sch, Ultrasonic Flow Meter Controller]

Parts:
C18, C20, C24, C31, C32: GRM155R71C104KA88D; 0402; TOLERANCE_% 10; PARTNUMBER GRM155R71C104KA88D
C21, C28, C35: GRM188R61C225KE15D; 0603; TOLERANCE_% 10; PARTNUMBER GRM188R61C225KE15D
C22, C27, C30: CL10B105KO8NNNC; 0603L; TOLERANCE_% 10; PARTNUMBER CL10B105KO8NNNC
C25, C26: CL21B106KPQNNNE; 0805_HV; TOLERANCE_% 10%; PARTNUMBER CL21B106KPQNNNE
C29: C0603C330J5GACTU; 0603L; TOLERANCE_% 5; PARTNUMBER C0603C330J5GACTU
C33, C34: GRM21BR61C105KA01L; 0805_HV; TOLERANCE_% 10%; PARTNUMBER GRM21BR61C105KA01L
C36: C0603C681J5GACTU; 0603L; TOLERANCE_% 5; PARTNUMBER C0603C681J5GACTU
C37: CC0603KRX7R7BB102; 0603L; TOLERANCE_% 10; PARTNUMBER CC0603KRX7R7BB102
FB1, FB2: MPZ1608S221A; 0603; PARTNUMBER MPZ1608S221A
R19, R20, R24, R27, R28, R29, R30, R39, R40, R41, R47, R50, R51, R59, R60, R62, R63, R64: RC0603FR-130RL; 0603L; TOLERANCE_% 5; PARTNUMBER RC0603FR-130RL
R23, R31, R32, R42, R53: RC0603FR-130RL; 0603L; TOLERANCE_% 5; PARTNUMBER RC0603FR-130RL; not fitted
R33, R34: RC0603FR-07806RL; 0603L; TOLERANCE_% 1; PARTNUMBER RC0603FR-07806RL
R35, R36: RC0603FR-07806RL; 0603L; TOLERANCE_% 1; PARTNUMBER RC0603FR-07806RL; not fitted
R37, R38, R52, R55: RC0603FR-072ML; 0603L; TOLERANCE_% 1; PARTNUMBER RC0603FR-072ML
R44, R56: RC0603FR-0724K9L; 0603L; TOLERANCE_% 1; PARTNUMBER RC0603FR-0724K9L
R45: RC0603FR-07200KL; 0603L; TOLERANCE_% 1; PARTNUMBER RC0603FR-07200KL; not fitted
R46, R48, R49: RC0603FR-101ML; 0603L; TOLERANCE_% 1%; PARTNUMBER RC0603FR-101ML
R54: RC0603FR-0710RL; 0603L; TOLERANCE_% 1; PARTNUMBER RC0603FR-0710RL
R57: RC0603FR-131K82L; 0603L; TOLERANCE_% 1; PARTNUMBER RC0603FR-131K82L
R58: RCG060310K0FKEA; 0603L; TOLERANCE_% 1; PARTNUMBER RCG060310K0FKEA; not fitted
R61: RC0603FR-07499RL; 0603L; TOLERANCE_% 1; PARTNUMBER RC0603FR-07499RL
RX1: 5003; Keystone5003; PARTNUMBER 5003
RX_GND1: 5001; Keystone5001; PARTNUMBER 5001
SHIELD_RX1: 5001; Keystone5001; PARTNUMBER 5001
SHIELD_TX1: 5001; Keystone5001; PARTNUMBER 5001
TP1: 5003; Keystone5003; PARTNUMBER 5003
TP2: 5001; Keystone5001; PARTNUMBER 5001
TP4, TP5, TP6, TP7, TP8, TP9, TP10, TP11, TP12: TP_1mm
TX1: 5003; Keystone5003; PARTNUMBER 5003
TX_GND1: 5001; Keystone5001; PARTNUMBER 5001
U2: SN74LVC2T45DCTR; DCT0008A_N; PARTNUMBER SN74LVC2T45DCTR
U4, U7: TS5A9411DCKR; DCK0006A_N; PARTNUMBER TS5A9411DCKR
U5, U6: TPS22860DBVR; DBV0006A_N; PARTNUMBER TPS22860DBVR
U8: OPA836IDBVT; DBV0006A_N; PARTNUMBER OPA836IDBVT

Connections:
/TI Controller/AFE/3V3: C25.1, C26.1, R19.2, TP1.1, U5.4 (VIN), U5.5 (VBIAS), U6.4 (VIN), U6.5 (VBIAS)
/TI Controller/AFE/AFE_CH0_IN: C37.1, R39.2
/TI Controller/AFE/AFE_CH0_OUT: R20.1, R35.1, R40.2, R49.2
/TI Controller/AFE/AFE_CH1_IN: R42.2, R46.2
/TI Controller/AFE/AFE_CH1_OUT: R36.1, R41.2, R48.2
/TI Controller/AFE/DRV1: R33.1, U2.2 (A1)
/TI Controller/AFE/DRV2: R34.1, U2.3 (A2)
/TI Controller/AFE/PWRSRC_RX: C34.1, FB2.2, R63.1, TP12.1
/TI Controller/AFE/PWRSRC_TX: C33.1, FB1.2, R62.1, TP11.1
/TI Controller/AFE/RX_MUX: R60.2, U7.1 (IN)
/TI Controller/AFE/RX_PWRSW: R51.1, U6.6 (ON)
/TI Controller/AFE/SIGNAL_RX: C30.2, R34.2, R36.2, U7.5 (COM)
/TI Controller/AFE/SIGNAL_TX: C22.1, R33.2, R35.2, U4.5 (COM)
/TI Controller/AFE/TX_MUX: R47.1, U4.1 (IN)
/TI Controller/AFE/TX_PWRSW: R50.1, U5.6 (ON)
/TI Controller/AFE/X_CH0_IN: R27.2, R31.2, R39.1
/TI Controller/AFE/X_CH0_OUT: R28.2, R31.1, R40.1
/TI Controller/AFE/X_CH1_IN: R30.2, R32.1, R42.1
/TI Controller/AFE/X_CH1_OUT: R29.2, R32.2, R41.1
/TI Controller/CH0_IN: R27.1; also elsewhere on the board
/TI Controller/CH0_OUT: R28.1; also elsewhere on the board
/TI Controller/CH1_IN: R30.1; also elsewhere on the board
/TI Controller/CH1_OUT: R29.1; also elsewhere on the board
/TI Controller/RxEn: R59.2, TP8.1; also elsewhere on the board
/TI Controller/RxPwr: R51.2, TP4.1; also elsewhere on the board
/TI Controller/RxSel1: R47.2, TP9.1; also elsewhere on the board
/TI Controller/RxSel2: R60.1, TP10.1; also elsewhere on the board
/TI Controller/TxPwr: R50.2, TP6.1; also elsewhere on the board
/TI Controller/TxSel: TP5.1; also elsewhere on the board
/TI Controller/XPB0: R53.2, TP7.1; also elsewhere on the board
unnamed: C21.2, R37.2, R38.2, R44.1
unnamed: C22.2, R44.2, R45.1
unnamed: C27.2, R54.1
unnamed: C28.2, R52.1, R53.1, R55.2, R56.1
unnamed: C36.1, R61.2, R64.2
unnamed: C37.2, R64.1
unnamed: R20.2, R23.1, U2.7 (B1)
unnamed: R23.2, R24.2, U2.6 (B2)
unnamed: TX1.1, U4.4 (NC), U7.6 (NO)
unnamed: RX1.1, U4.6 (NO), U7.4 (NC)
unnamed: FB1.1, U5.1 (VOUT)
unnamed: FB2.1, U6.1 (VOUT)
unnamed: C30.1, R56.2, U8.3 (VIN+)
unnamed: C29.2, R54.2, R57.1, U8.4 (VIN-)
unnamed: C29.1, R57.2, R61.1, U8.1 (VOUT)
unnamed: R58.2, R59.1, U8.5 (~PD)
USS_GND: C18.2, C20.1, C21.1, C24.1, C25.2, C26.2, C27.1, C28.1, C31.1, C32.1, C33.2, C34.2, C35.2, C36.2, R24.1, R37.1, R38.1, R45.2, R46.1, R48.1, R49.1, R55.1, RX_GND1.1, SHIELD_RX1.1, SHIELD_TX1.1, TP2.1, TX_GND1.1, U2.4 (GND), U2.5 (DIR), U4.3 (GND), U5.2 (GND), U6.2 (GND), U7.3 (GND), U8.2 (VS-); also elsewhere on the board
VCC-RX: C18.1, C32.2, C35.1, R52.2, R58.1, R63.2, U2.8 (VCCB), U8.6 (VS+)
VCC-TX: C20.2, C24.2, C31.2, R62.2, U2.1 (VCCA), U4.2 (V+), U7.2 (V+)
VCC_3V3: R19.1; also elsewhere on the board

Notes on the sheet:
INPUT IMPEDANCE
FOR GAS TERMINATION
-3dB@584KHz
AFE SIGNAL TEST POINTS
FOR TX SENSOR
THE SHIELDING SHOULD BE MASKED INTO A GUARD TRACE AROUND THE SIGNAL
TRY TO MATCH OPA836
Off Sheet Connection
FOR RX SENSOR

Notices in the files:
UART Firmware/FR6043_USSSWLib_template_example/ussSWLib/USS_HAL/USS_Lib_HAL.c:
--COPYRIGHT--,TI
nifest and you access "on-line", as well as any updates or upgrades to such software programs or documentation, if any, provided to you at TI's sole discretion.  The Licensed Materials are specifically designed and licensed for use solely and exclusively with MSP microcontroller devices manufactured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
Warranties and Limitations.  THE LICENSED MATERIALS ARE PROVIDED "AS IS".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
README.md:
License: MIT
